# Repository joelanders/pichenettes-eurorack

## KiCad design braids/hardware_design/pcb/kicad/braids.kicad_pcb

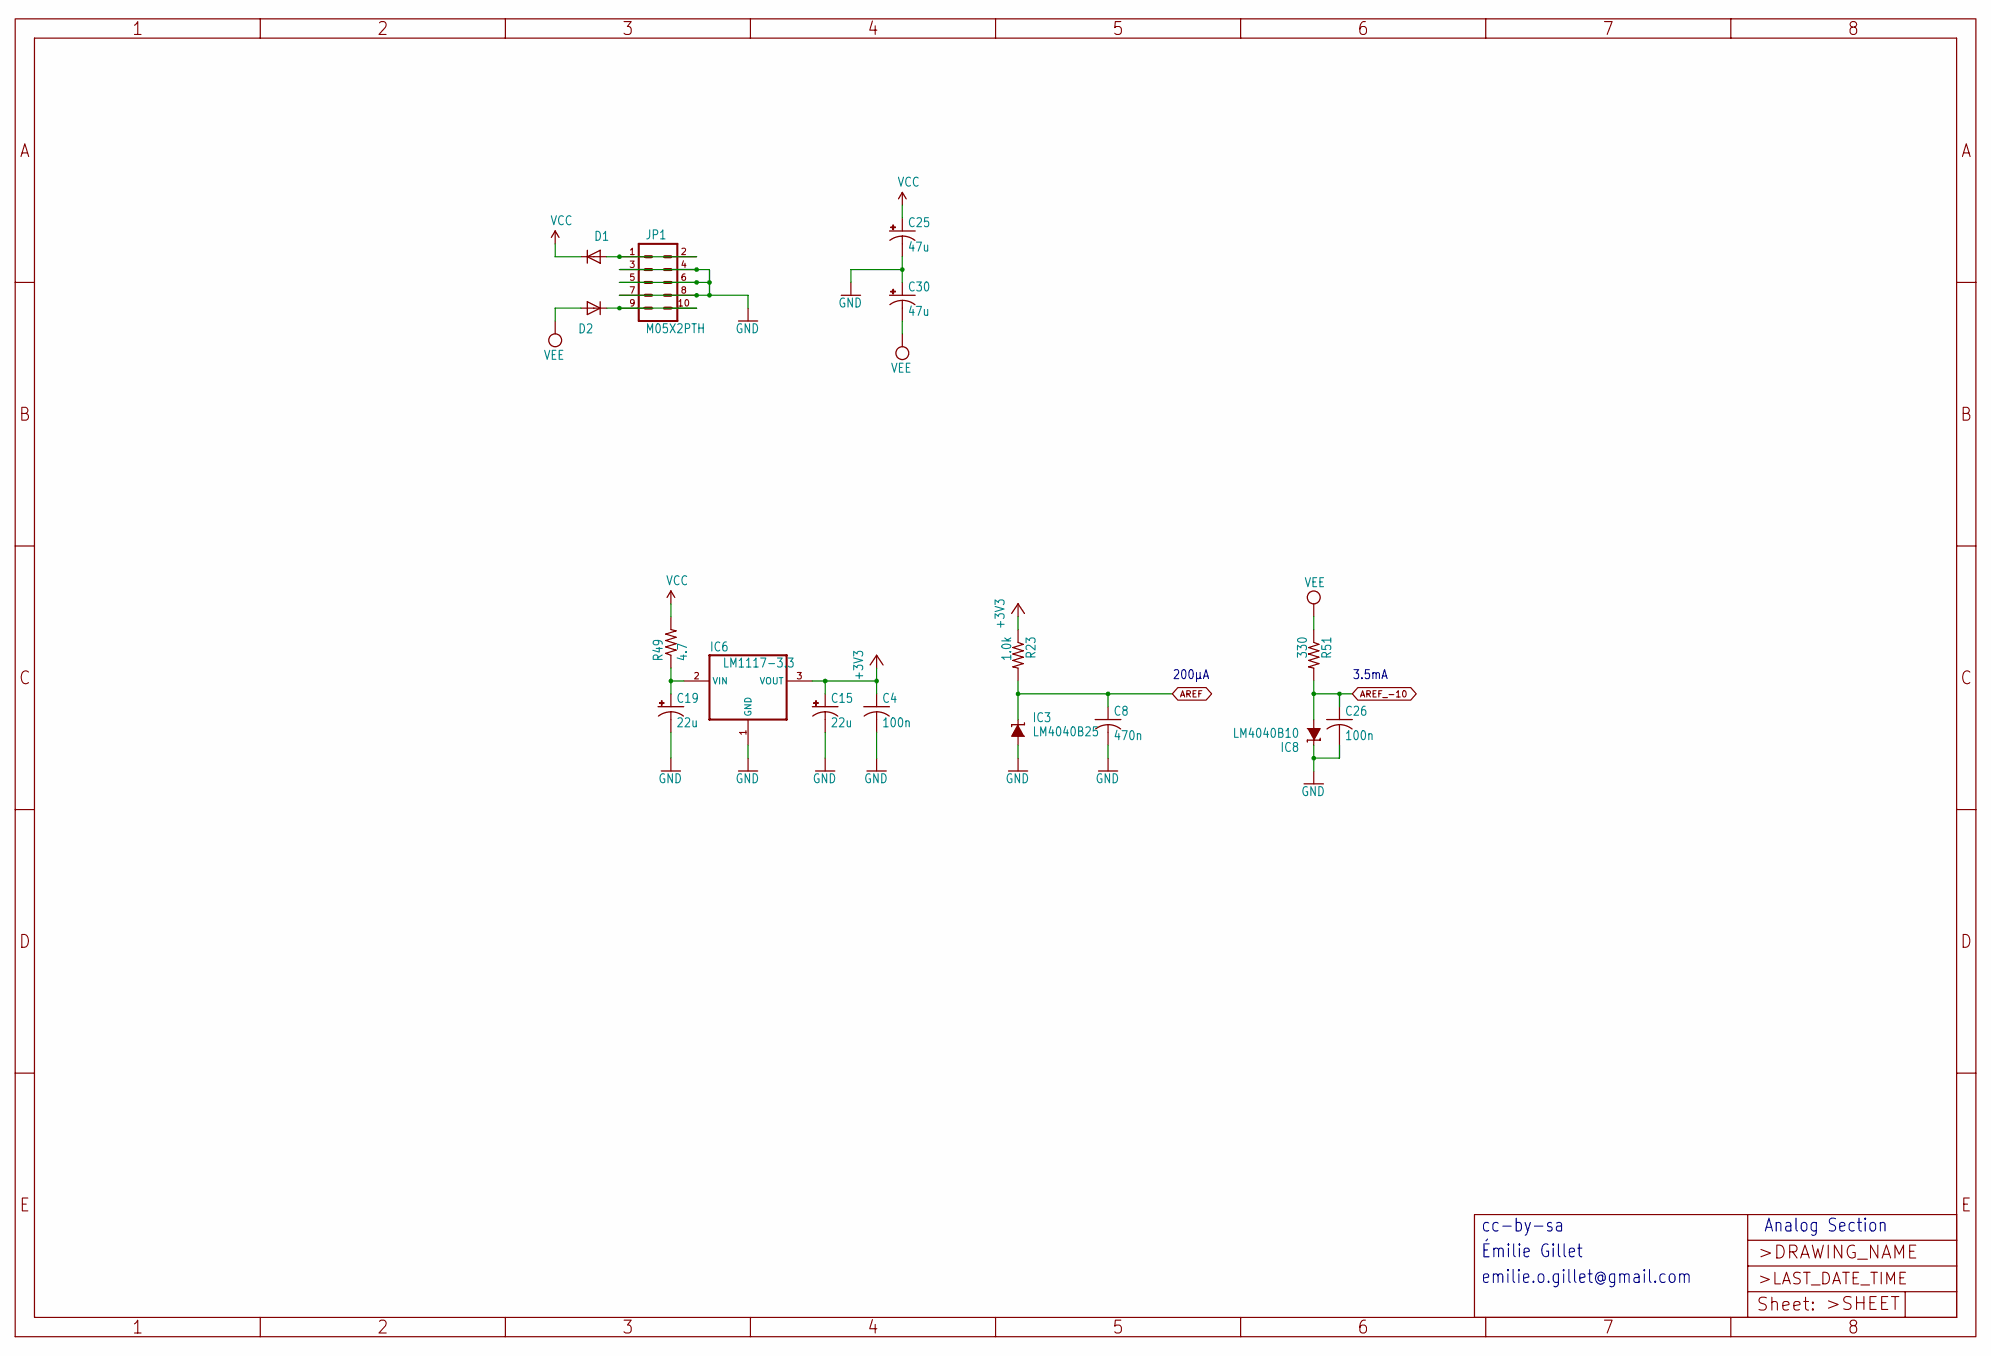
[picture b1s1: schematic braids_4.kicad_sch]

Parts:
C4, C26: 100n; C0603
C8: 470n; C0603
C15, C19: 22u; PANASONIC_C
C25, C30: 47u; PANASONIC_D
D1, D2: 1N5819HW; SOD123
IC3: LM4040B25; DBZ_R-PDSO-G3
IC6: LM1117-3.3; TO252
IC8: LM4040B10; DBZ_R-PDSO-G3
JP1: M05X2PTH; AVR_ICSP
R23: 1.0k; R0603
R49: 4.7; R1206
R51: 330; R0603

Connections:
+3V3: C4.1, C15.+, IC6.3 (VOUT), R23.1; also elsewhere on the board
AREF: C8.1, IC3.1 (C), R23.2; also elsewhere on the board
AREF_-10: C26.1, IC8.2 (A), R51.2; also elsewhere on the board
GND: C4.2, C8.2, C15.-, C19.-, C25.-, C26.2, C30.+, IC3.2 (A), IC6.1 (GND), IC8.1 (C), JP1.3, JP1.4, JP1.5, JP1.6, JP1.7, JP1.8; also elsewhere on the board
unnamed: C19.+, IC6.2 (VIN), R49.1
unnamed: D1.A, JP1.1, JP1.2
unnamed: D2.C, JP1.9, JP1.10
VCC: C25.+, D1.C, R49.2; also elsewhere on the board
VEE: C30.-, D2.A, R51.1; also elsewhere on the board

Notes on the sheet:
200µA
Analog Section
cc-by-sa
3.5mA
emilie.o.gillet@gmail.com
Émilie Gillet

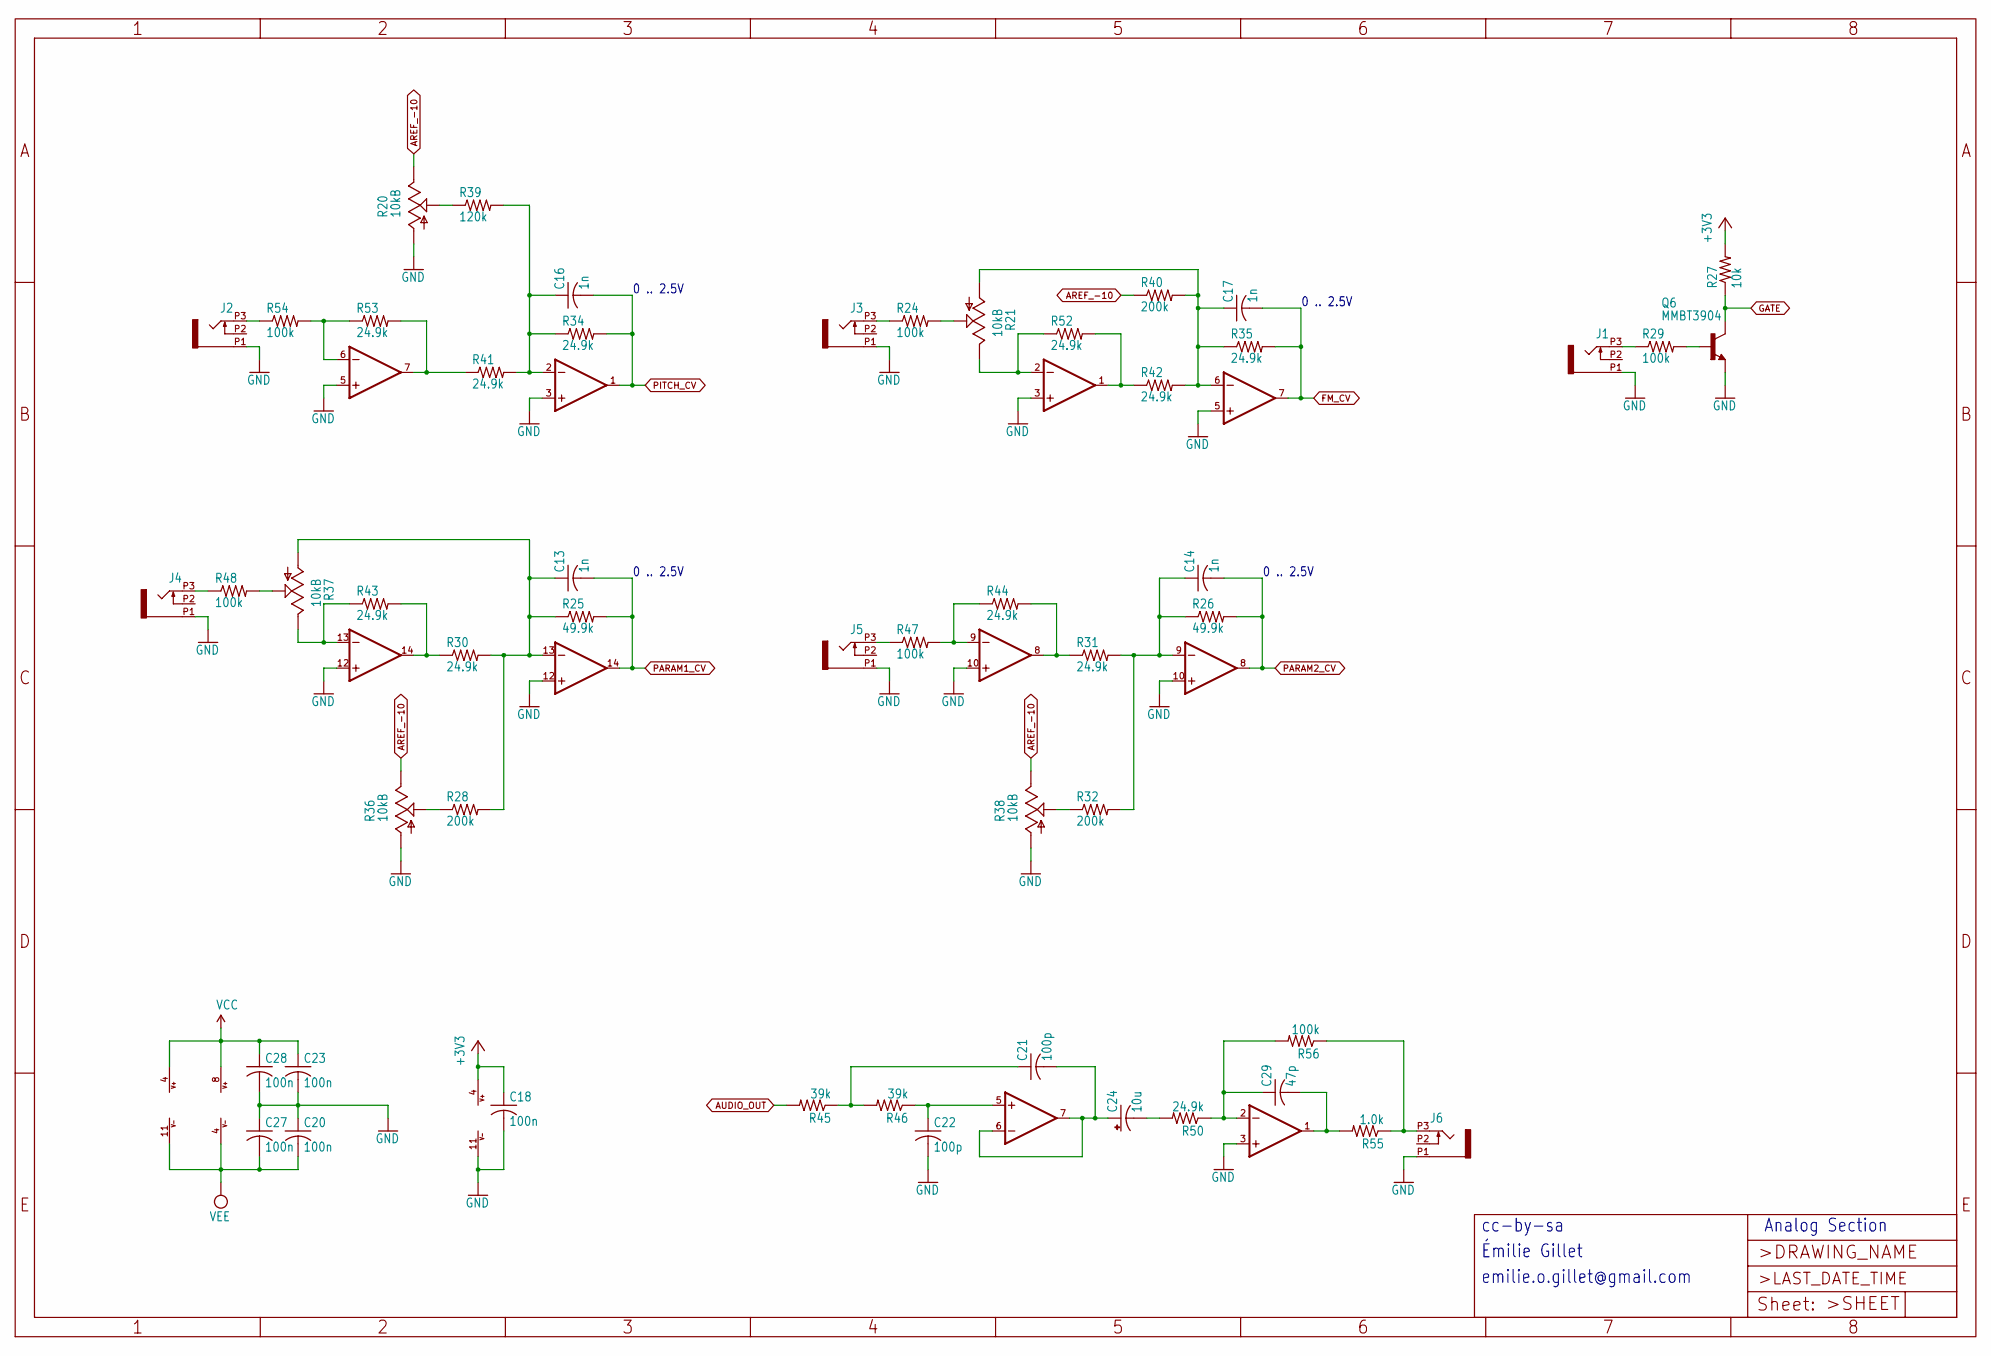
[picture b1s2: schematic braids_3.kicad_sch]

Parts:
C13, C14, C16, C17: 1n; C0603
C18, C20, C23, C27, C28: 100n; C0603
C21, C22: 100p; C0603
C24: 10u; PANASONIC_B
C29: 47p; C0603
IC7: MCP6004; SO14
IC9: TL074D; SO14
IC10: TL072; SO08
J1, J2, J3, J4, J5, J6: PJ301_THONKICONN6; WQP_PJ_301M6
Q6: MMBT3904; SOT23-BEC
R20, R21, R36, R37, R38: 10kB; ALPS_POT_VERTICAL_PS
R24, R29, R47, R48, R54, R56: 100k; R0603
R25, R26: 49.9k; R0603
R27: 10k; R0603
R28, R32, R40: 200k; R0603
R30, R31, R34, R35, R41, R42, R43, R44, R50, R52, R53: 24.9k; R0603
R39: 120k; R0603
R45, R46: 39k; R0603
R55: 1.0k; R0603

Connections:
+3V3: C18.1, IC7.4 (V+), R27.2; also elsewhere on the board
AREF_-10: R20.P$1 (E), R36.P$1 (E), R38.P$1 (E), R40.1; also elsewhere on the board
AUDIO_OUT: R45.2; also elsewhere on the board
FM_CV: C17.2, IC7.7 (OUT), R35.2; also elsewhere on the board
GATE: Q6.C, R27.1; also elsewhere on the board
GND: C18.2, C20.1, C22.2, C23.2, C27.1, C28.2, IC7.3 (+IN), IC7.5 (+IN), IC7.10 (+IN), IC7.11 (V-), IC7.12 (+IN), IC9.3 (+IN), IC9.5 (+IN), IC9.10 (+IN), IC9.12 (+IN), IC10.3 (+IN), J1.P1 (1), J2.P1 (1), J3.P1 (1), J4.P1 (1), J5.P1 (1), J6.P1 (1), Q6.E, R20.P$3 (A), R36.P$3 (A), R38.P$3 (A); also elsewhere on the board
unnamed: C13.1, IC7.13 (-IN), R25.1, R28.2, R30.2, R37.P$3 (A)
unnamed: C14.1, IC7.9 (-IN), R26.1, R31.2, R32.2
unnamed: C16.1, IC7.2 (-IN), R34.1, R39.2, R41.2
unnamed: C17.1, IC7.6 (-IN), R21.P$3 (A), R35.1, R40.2, R42.2
unnamed: C21.1, R45.1, R46.2
unnamed: C21.2, C24.+, IC10.6 (-IN), IC10.7 (OUT)
unnamed: C22.1, IC10.5 (+IN), R46.1
unnamed: C24.-, R50.2
unnamed: C29.1, IC10.2 (-IN), R50.1, R56.2
unnamed: C29.2, IC10.1 (OUT), R55.2
unnamed: IC9.1 (OUT), R42.1, R52.2
unnamed: IC9.2 (-IN), R21.P$1 (E), R52.1
unnamed: IC9.6 (-IN), R53.1, R54.2
unnamed: IC9.7 (OUT), R41.1, R53.2
unnamed: IC9.8 (OUT), R31.1, R44.2
unnamed: IC9.9 (-IN), R44.1, R47.2
unnamed: IC9.13 (-IN), R37.P$1 (E), R43.1
unnamed: IC9.14 (OUT), R30.1, R43.2
unnamed: J1.P3 (3), R29.1
unnamed: J2.P3 (3), R54.1
unnamed: J3.P3 (3), R24.1
unnamed: J4.P3 (3), R48.1
unnamed: J5.P3 (3), R47.1
unnamed: J6.P3 (3), R55.1, R56.1
unnamed: Q6.B, R29.2
unnamed: R20.P$2 (S), R39.1
unnamed: R21.P$2 (S), R24.2
unnamed: R28.1, R36.P$2 (S)
unnamed: R32.1, R38.P$2 (S)
unnamed: R37.P$2 (S), R48.2
PARAM1_CV: C13.2, IC7.14 (OUT), R25.2; also elsewhere on the board
PARAM2_CV: C14.2, IC7.8 (OUT), R26.2; also elsewhere on the board
PITCH_CV: C16.2, IC7.1 (OUT), R34.2; also elsewhere on the board
VCC: C23.1, C28.1, IC9.4 (V+), IC10.8 (V+); also elsewhere on the board
VEE: C20.2, C27.2, IC9.11 (V-), IC10.4 (V-); also elsewhere on the board

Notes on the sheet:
Émilie Gillet
0 .. 2.5V
cc-by-sa
emilie.o.gillet@gmail.com
Analog Section

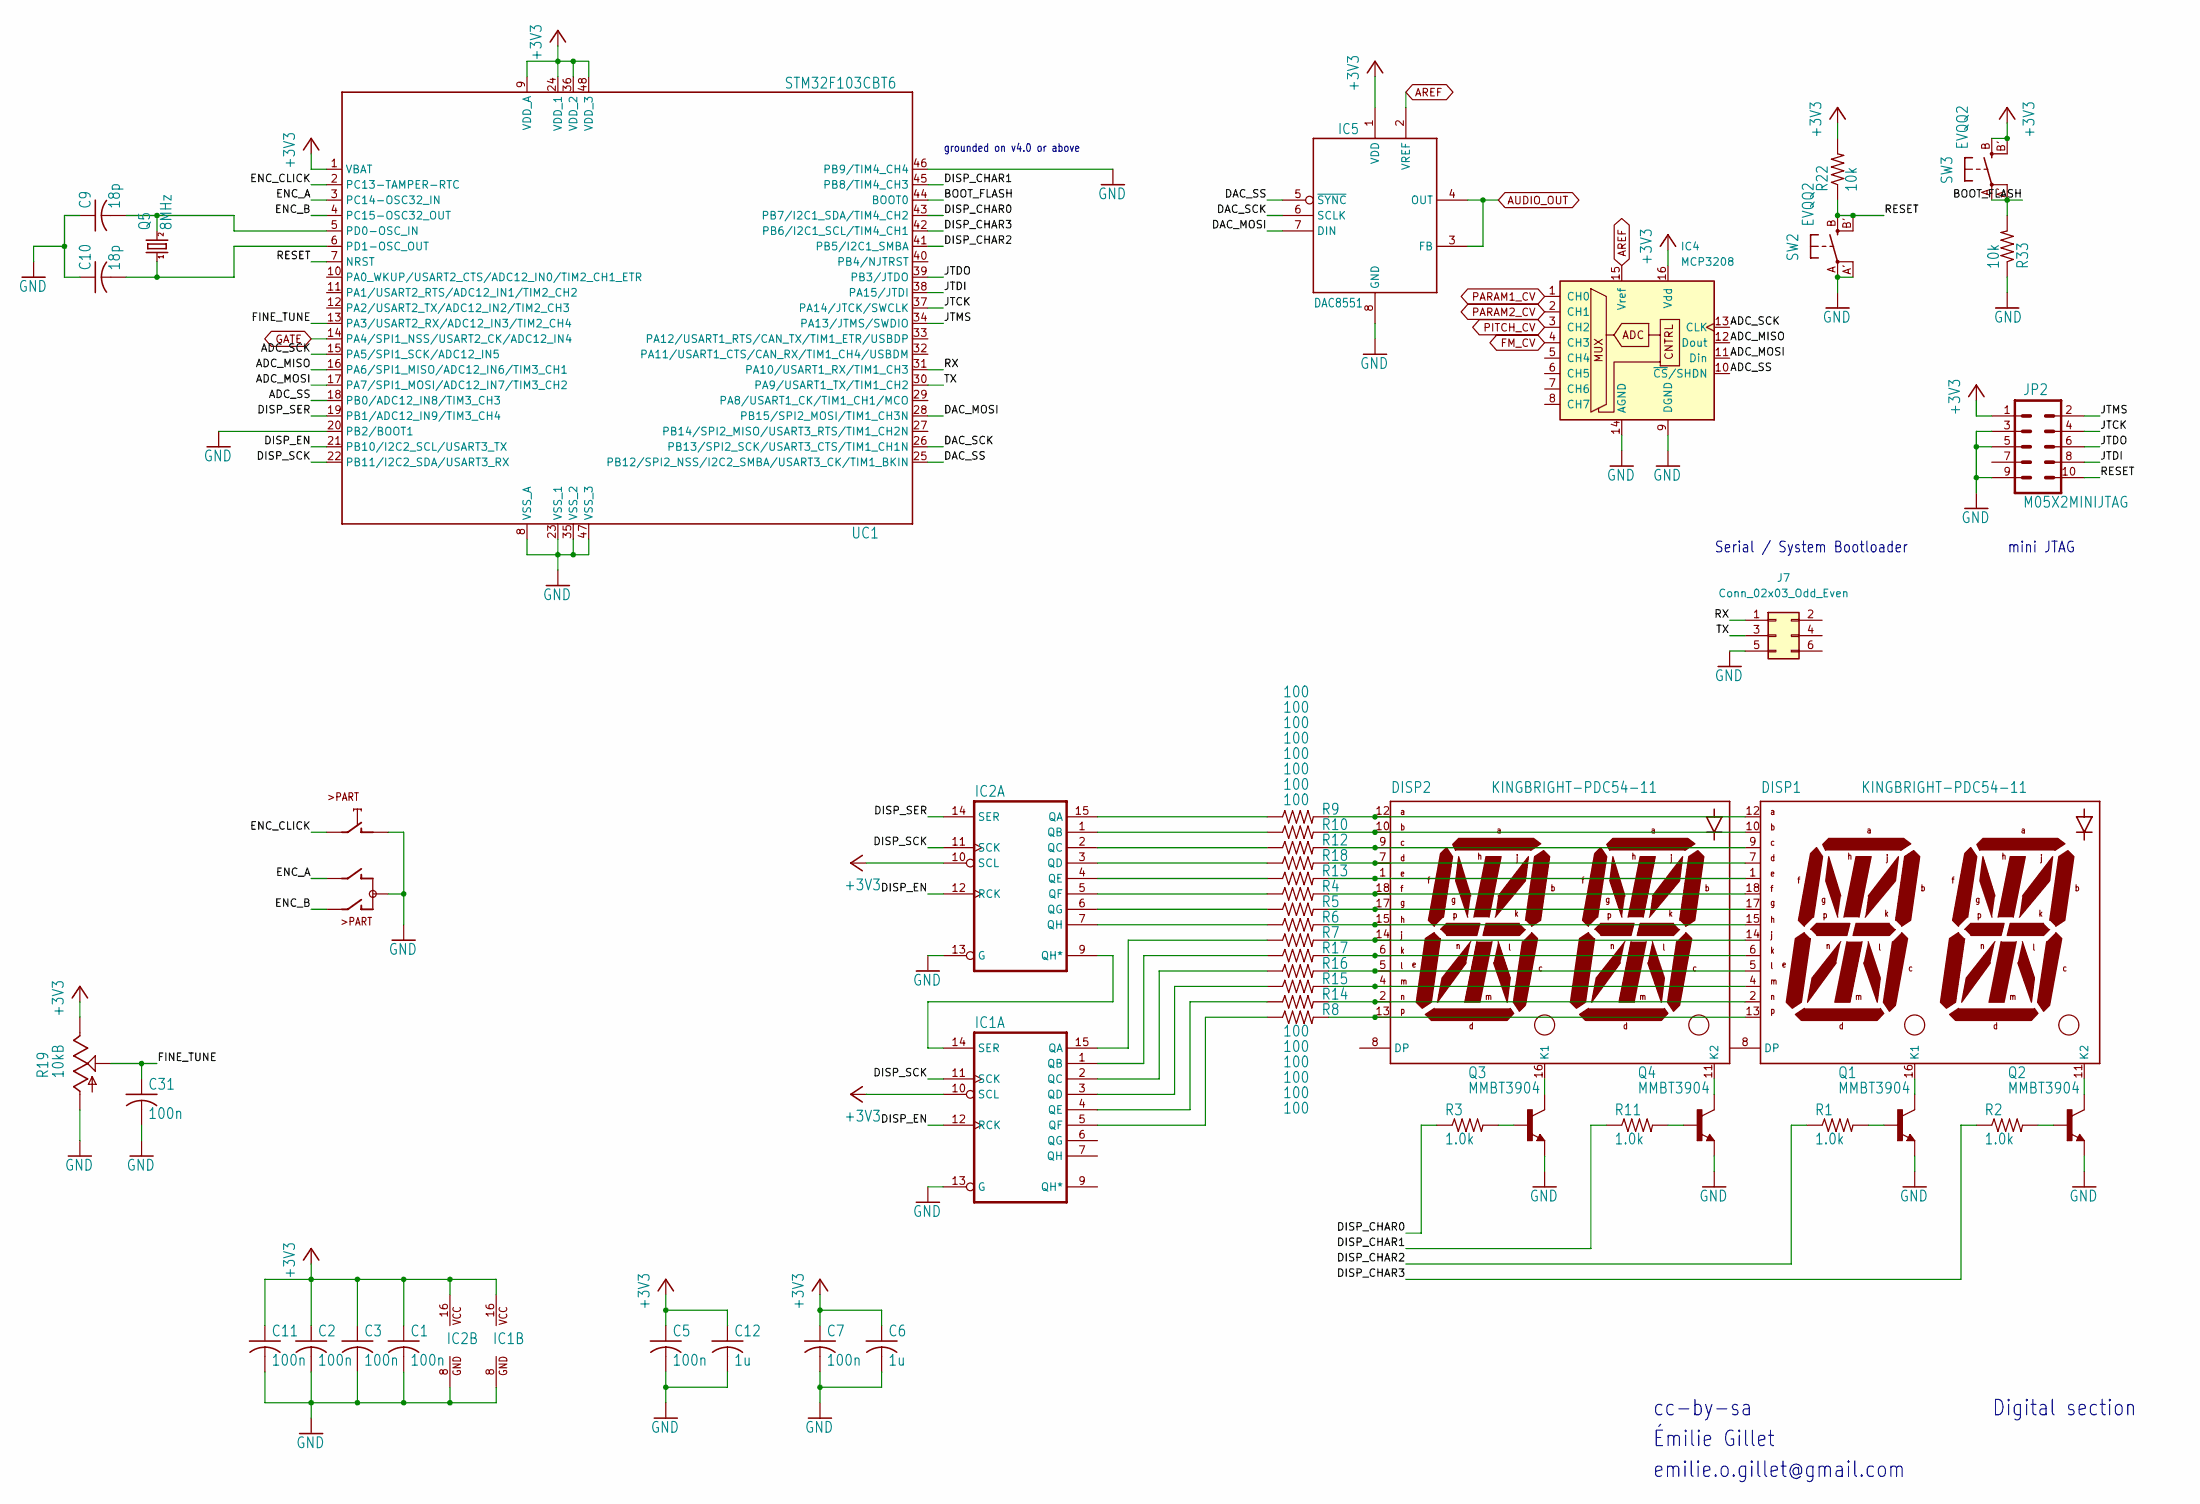
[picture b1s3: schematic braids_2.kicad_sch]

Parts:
C1, C2, C3, C5, C7, C11, C31: 100n; C0603
C6, C12: 1u; C0603
C9, C10: 18p; C0603
DISP1, DISP2: KINGBRIGHT-PDC54-11; PDC54
IC1, IC2: 74595D; SO16
IC4: MCP3208; SOIC-16_3.9x9.9mm_P1.27mm
IC5: DAC8551; MSOP-8
J7: Conn_02x03_Odd_Even; PinHeader_2x03_P2.54mm_Horizontal_SMD
JP2: M05X2MINIJTAG; AVR_ICSP
Q1, Q2, Q3, Q4: MMBT3904; SOT23-BEC
Q5: 8MHz; HC49UP
R1, R2, R3, R11: 1.0k; R0603
R4, R5, R6, R7, R8, R9, R10, R12, R13, R14, R15, R16, R17, R18: 100; R0603
R19: 10kB; ALPS_POT_VERTICAL_PS
R22, R33: 10k; R0603
SW1: EC12E_SW; ALPS_EC12E_SW
SW2, SW3: EVQQ2; EVQ-Q2
UC1: STM32F103CBT6; LQFP48

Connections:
+3V3: C1.1, C2.1, C3.1, C5.1, C6.1, C7.1, C11.1, C12.1, IC1.10 (SCL), IC1.16 (VCC), IC2.10 (SCL), IC2.16 (VCC), IC4.16 (Vdd), IC5.1 (VDD), JP2.1, R19.P$1 (E), R22.2, SW3.B (S), SW3.B' (S1), UC1.1 (VBAT), UC1.9 (VDD_A), UC1.24 (VDD_1), UC1.36 (VDD_2), UC1.48 (VDD_3); also elsewhere on the board
/braids_2/ADC_MISO: IC4.12 (Dout), UC1.16 (PA6/SPI1_MISO/ADC12_IN6/TIM3_CH1)
/braids_2/ADC_MOSI: IC4.11 (Din), UC1.17 (PA7/SPI1_MOSI/ADC12_IN7/TIM3_CH2)
/braids_2/ADC_SCK: IC4.13 (CLK), UC1.15 (PA5/SPI1_SCK/ADC12_IN5)
/braids_2/ADC_SS: IC4.10 (~CS/SHDN), UC1.18 (PB0/ADC12_IN8/TIM3_CH3)
/braids_2/BOOT_FLASH: R33.2, SW3.A, SW3.A' (P1), UC1.44 (BOOT0)
/braids_2/DAC_MOSI: IC5.7 (DIN), UC1.28 (PB15/SPI2_MOSI/TIM1_CH3N)
/braids_2/DAC_SCK: IC5.6 (SCLK), UC1.26 (PB13/SPI2_SCK/USART3_CTS/TIM1_CH1N)
/braids_2/DAC_SS: IC5.5 (~SYNC), UC1.25 (PB12/SPI2_NSS/I2C2_SMBA/USART3_CK/TIM1_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)
/braids_2/DISP_CHAR0: R3.1, UC1.43 (PB7/I2C1_SDA/TIM4_CH2)
/braids_2/DISP_CHAR1: R11.1, UC1.45 (PB8/TIM4_CH3)
/braids_2/DISP_CHAR2: R1.1, UC1.41 (PB5/I2C1_SMBA)
/braids_2/DISP_CHAR3: R2.1, UC1.42 (PB6/I2C1_SCL/TIM4_CH1)
/braids_2/DISP_EN: IC1.12 (RCK), IC2.12 (RCK), UC1.21 (PB10/I2C2_SCL/USART3_TX)
/braids_2/DISP_SCK: IC1.11 (SCK), IC2.11 (SCK), UC1.22 (PB11/I2C2_SDA/USART3_RX)
/braids_2/DISP_SER: IC2.14 (SER), UC1.19 (PB1/ADC12_IN9/TIM3_CH4)
/braids_2/ENC_A: SW1.B, UC1.3 (PC14-OSC32_IN)
/braids_2/ENC_B: SW1.A, UC1.4 (PC15-OSC32_OUT)
/braids_2/ENC_CLICK: SW1.E (2), UC1.2 (PC13-TAMPER-RTC)
/braids_2/FINE_TUNE: C31.1, R19.P$2 (S), UC1.13 (PA3/USART2_RX/ADC12_IN3/TIM2_CH4)
/braids_2/JTCK: JP2.4, UC1.37 (PA14/JTCK/SWCLK)
/braids_2/JTDI: JP2.8, UC1.38 (PA15/JTDI)
/braids_2/JTDO: JP2.6, UC1.39 (PB3/JTDO)
/braids_2/JTMS: JP2.2, UC1.34 (PA13/JTMS/SWDIO)
/braids_2/RESET: JP2.10, R22.1, SW2.B (S), SW2.B' (S1), UC1.7 (NRST)
/braids_2/RX: J7.1, UC1.31 (PA10/USART1_RX/TIM1_CH3)
/braids_2/TX: J7.3, UC1.30 (PA9/USART1_TX/TIM1_CH2)
AREF: IC4.15 (Vref), IC5.2 (VREF); also elsewhere on the board
AUDIO_OUT: IC5.3 (FB), IC5.4 (OUT); also elsewhere on the board
FM_CV: IC4.4 (CH3); also elsewhere on the board
GATE: UC1.14 (PA4/SPI1_NSS/USART2_CK/ADC12_IN4); also elsewhere on the board
GND: C1.2, C2.2, C3.2, C5.2, C6.2, C7.2, C9.1, C10.1, C11.2, C12.2, C31.2, IC1.8 (GND), IC1.13 (G), IC2.8 (GND), IC2.13 (G), IC4.9 (DGND), IC4.14 (AGND), IC5.8 (GND), J7.5, JP2.3, JP2.5, JP2.9, Q1.E, Q2.E, Q3.E, Q4.E, R19.P$3 (A), R33.1, SW1.C, SW1.D (1), SW2.A, SW2.A' (P1), UC1.8 (VSS_A), UC1.20 (PB2/BOOT1), UC1.23 (VSS_1), UC1.35 (VSS_2), UC1.46 (PB9/TIM4_CH4), UC1.47 (VSS_3); also elsewhere on the board
unnamed: C9.2, Q5.2, UC1.5 (PD0-OSC_IN)
unnamed: C10.2, Q5.1, UC1.6 (PD1-OSC_OUT)
unnamed: DISP1.1 (E), DISP2.1 (E), R13.2
unnamed: DISP1.2 (N), DISP2.2 (N), R14.2
unnamed: DISP1.4 (M), DISP2.4 (M), R15.2
unnamed: DISP1.5 (L), DISP2.5 (L), R16.2
unnamed: DISP1.6 (K), DISP2.6 (K), R17.2
unnamed: DISP1.7 (D), DISP2.7 (D), R18.2
unnamed: DISP1.9 (C), DISP2.9 (C), R12.2
unnamed: DISP1.10 (B), DISP2.10 (B), R10.2
unnamed: DISP1.11 (K2), Q2.C
unnamed: DISP1.12 (A), DISP2.12 (A), R9.2
unnamed: DISP1.13, DISP2.13, R8.2
unnamed: DISP1.14 (J), DISP2.14 (J), R7.2
unnamed: DISP1.15 (H), DISP2.15 (H), R6.2
unnamed: DISP1.16 (K1), Q1.C
unnamed: DISP1.17 (G), DISP2.17 (G), R5.2
unnamed: DISP1.18 (F), DISP2.18 (F), R4.2
unnamed: DISP2.11 (K2), Q4.C
unnamed: DISP2.16 (K1), Q3.C
unnamed: IC1.1 (QB), R17.1
unnamed: IC1.2 (QC), R16.1
unnamed: IC1.3 (QD), R15.1
unnamed: IC1.4 (QE), R14.1
unnamed: IC1.5 (QF), R8.1
unnamed: IC1.14 (SER), IC2.9 (QH*)
unnamed: IC1.15 (QA), R7.1
unnamed: IC2.1 (QB), R10.1
unnamed: IC2.2 (QC), R12.1
unnamed: IC2.3 (QD), R18.1
unnamed: IC2.4 (QE), R13.1
unnamed: IC2.5 (QF), R4.1
unnamed: IC2.6 (QG), R5.1
unnamed: IC2.7 (QH), R6.1
unnamed: IC2.15 (QA), R9.1
unnamed: Q1.B, R1.2
unnamed: Q2.B, R2.2
unnamed: Q3.B, R3.2
unnamed: Q4.B, R11.2
PARAM1_CV: IC4.1 (CH0); also elsewhere on the board
PARAM2_CV: IC4.2 (CH1); also elsewhere on the board
PITCH_CV: IC4.3 (CH2); also elsewhere on the board

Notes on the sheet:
Digital section
Émilie Gillet
emilie.o.gillet@gmail.com
mini JTAG
Serial / System Bootloader
grounded on v4.0 or above
cc-by-sa

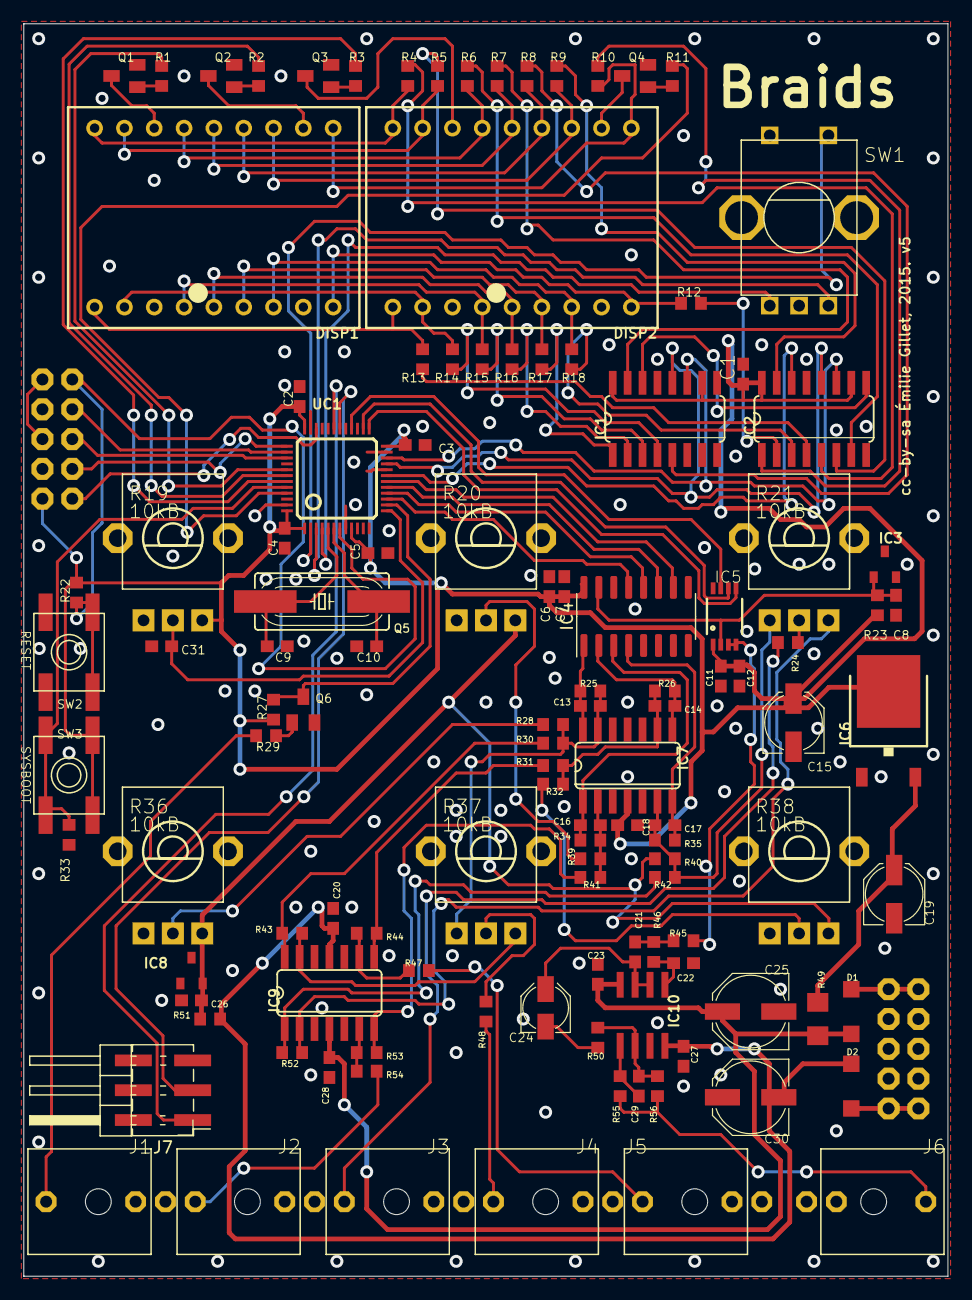
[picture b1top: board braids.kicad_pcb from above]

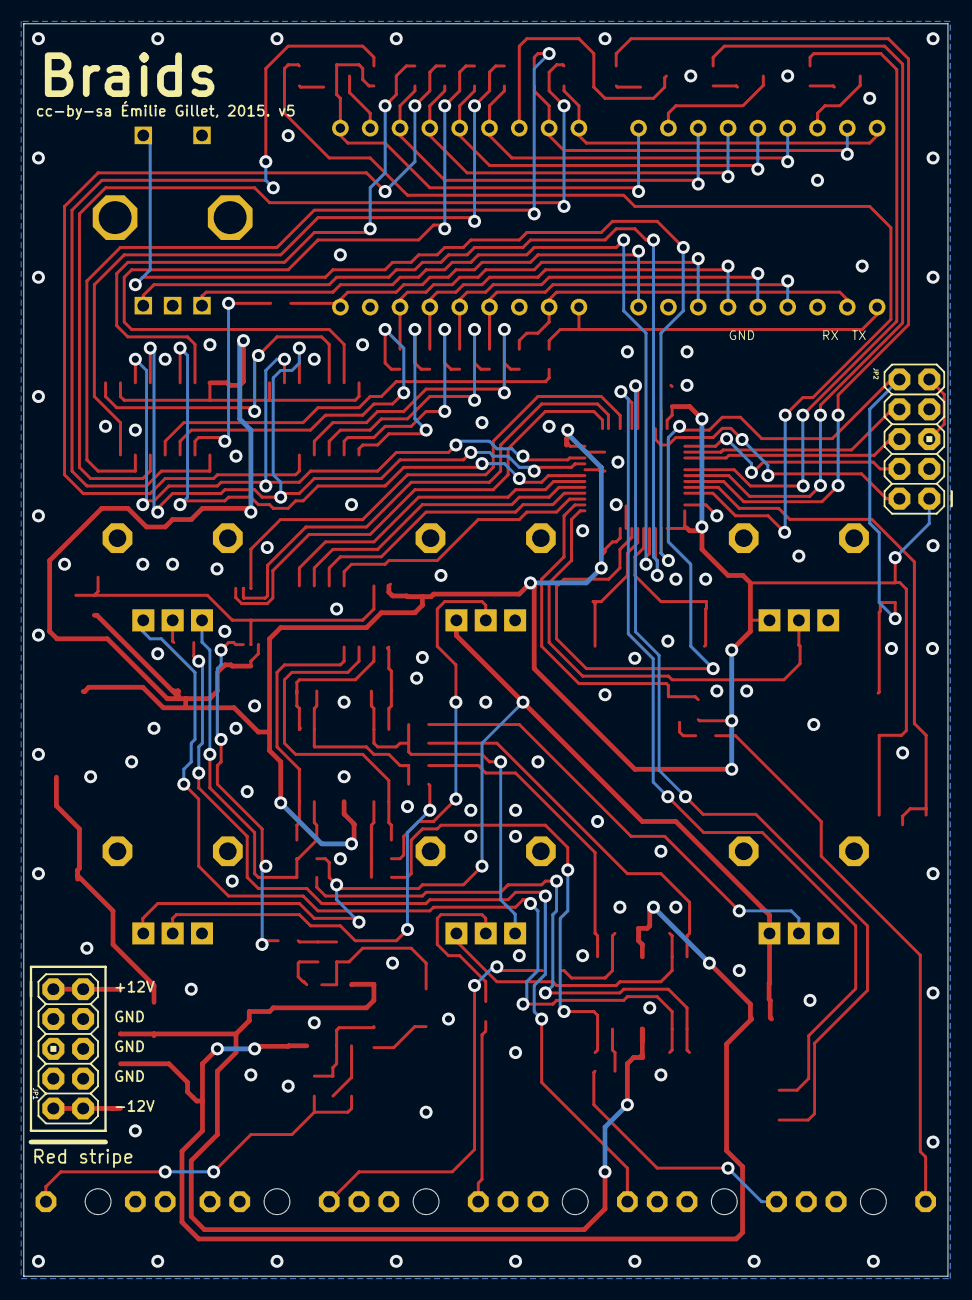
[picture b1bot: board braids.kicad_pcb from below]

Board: 2 copper layers, 78.7 x 106.7 mm, 120 parts (2 on the bottom side), 110 nets.

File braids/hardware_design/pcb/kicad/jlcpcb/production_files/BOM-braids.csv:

Comment,Designator,Footprint,LCSC
1n,C16,C0603,
100,R5,R0603,
24.9k,R41,R0603,
10kB,R19,ALPS_POT_VERTICAL_PS,
10kB,R36,ALPS_POT_VERTICAL_PS,
1.0k,R3,R0603,
200k,R32,R0603,
100n,C11,C0603,
MMBT3904,Q2,SOT23-BEC,
100,R18,R0603,
100p,C22,C0603,
8MHz,Q5,HC49UP,
100,R13,R0603,
TL074D,IC9,SO14,
330,R51,R0603,
1u,C6,C0603,
LM4040B25,IC3,DBZ_R-PDSO-G3,
100,R17,R0603,
100n,C4,C0603,
100n,C28,C0603,
47u,C30,PANASONIC_D,
MMBT3904,Q6,SOT23-BEC,
100n,C7,C0603,
74595D,IC2,SO16,
1.0k,R55,R0603,
LM4040B10,IC8,DBZ_R-PDSO-G3,
10k,R27,R0603,
1.0k,R23,R0603,
10k,R22,R0603,
100n,C1,C0603,
1.0k,R1,R0603,
100,R12,R0603,
PJ301_THONKICONN6,J4,WQP_PJ_301M6,
24.9k,R53,R0603,
PJ301_THONKICONN6,J3,WQP_PJ_301M6,
EVQQ2,SW2,EVQ-Q2,
MCP3204,IC4,SO14,
MMBT3904,Q3,SOT23-BEC,
24.9k,R50,R0603,
PJ301_THONKICONN6,J5,WQP_PJ_301M6,
24.9k,R42,R0603,
100,R7,R0603,
DAC8551,IC5,MSOP-8,
200k,R28,R0603,
PJ301_THONKICONN6,J1,WQP_PJ_301M6,
100n,C18,C0603,
100,R14,R0603,
100n,C3,C0603,
PJ301_THONKICONN6,J2,WQP_PJ_301M6,
47u,C25,PANASONIC_D,
470n,C8,C0603,
STM32F103CBT6,UC1,LQFP48,
100n,C26,C0603,
1n,C17,C0603,
1.0k,R2,R0603,
1n,C13,C0603,
100,R16,R0603,
100n,C27,C0603,
24.9k,R35,R0603,
24.9k,R34,R0603,
100,R8,R0603,
47p,C29,C0603,
74595D,IC1,SO16,
100,R6,R0603,
MMBT3904,Q4,SOT23-BEC,
100k,R47,R0603,
EC12E_SW,SW1,ALPS_EC12E_SW,
10kB,R20,ALPS_POT_VERTICAL_PS,
Conn_02x03_Odd_Even,J7,PinHeader_2x03_P2.54mm_Horizontal_SMD,
KINGBRIGHT-PDC54-11,DISP1,PDC54,
39k,R46,R0603,
100n,C5,C0603,
100k,R56,R0603,
22u,C19,PANASONIC_C,
24.9k,R44,R0603,
24.9k,R52,R0603,
49.9k,R25,R0603,
100k,R24,R0603,
24.9k,R30,R0603,
24.9k,R43,R0603,
1n,C14,C0603,
10kB,R38,ALPS_POT_VERTICAL_PS,
4.7,R49,R1206,
10kB,R37,ALPS_POT_VERTICAL_PS,
LM1117-3.3,IC6,TO252,
MCP6004,IC7,SO14,
39k,R45,R0603,
1N5819HW,D2,SOD123,
10kB,R21,ALPS_POT_VERTICAL_PS,
24.9k,R31,R0603,
EVQQ2,SW3,EVQ-Q2,
100,R10,R0603,
1u,C12,C0603,
49.9k,R26,R0603,
PJ301_THONKICONN6,J6,WQP_PJ_301M6,
10u,C24,PANASONIC_B,
10k,R33,R0603,
100p,C21,C0603,
100,R4,R0603,
100k,R48,R0603,
200k,R40,R0603,
1N5819HW,D1,SOD123,
100,R9,R0603,
KINGBRIGHT-PDC54-11,DISP2,PDC54,
18p,C10,C0603,
18p,C9,C0603,
MMBT3904,Q1,SOT23-BEC,
100n,C31,C0603,
120k,R39,R0603,
100k,R29,R0603,
100n,C20,C0603,
100n,C23,C0603,
22u,C15,PANASONIC_C,
100n,C2,C0603,
1.0k,R11,R0603,
100,R15,R0603,
100k,R54,R0603,
TL072,IC10,SO08,
M05X2PTH,JP1,AVR_ICSP,
M05X2MINIJTAG,JP2,AVR_ICSP,

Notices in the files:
braids/hardware_design/pcb/kicad/braids.kicad_pcb:
cc-by-sa Émilie Gillet, 2015. v5
clouds/hardware_design/pcb/kicad/clouds.kicad_pcb:
cc-by-sa Émilie Gillet, 2015. v3
elements/hardware_design/pcb/kicad/elements.kicad_pcb:
cc-by-sa Émilie Gillet, 2014. v0.2
